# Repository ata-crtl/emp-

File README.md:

**COMPLETE EMP BUILD**

  This is a low energy through hole electro magnetic pulse generator built for educational purposes.
  It uses inductive Kicback from a simple air core coil to generate broad band pulse that can glitch or reset unshielded digital circuits. Flip the top saftey , then you hold down the trigger for 2 seconds to fire max.

Onshape link = https://cad.onshape.com/documents/e3ea2a8dce756d3e28ba0ed2/w/b44164742f645132d3413e84/e/23451d8a78cdce11df78b1ae?renderMode=0&uiState=6a40249c9a392f71b3cf0f7e
  ---

 ## Table of Contents

- [What is this?](#what-is-this)
- [Why I built it](#why-i-built-it)
- [How it works (in 30 secs)](#how-it-works-in-30-secs)
- [Images and diagrams](#images-and-diagrams)
- [Assembly instructions](#assembly-instructions)
  - [1. Solder the PCB](#1-solder-the-pcb)
  - [2. Wind the coil](#2-wind-the-coil)
  - [3. Prepare the enclosure](#3-prepare-the-enclosure)
  - [4. Final assembly](#4-final-assembly)
- [Safety precautions](#safety-precautions)

---

## What is this?
 A compact, battery powered device that creates a rapid magnetic field collapse,radiating an electro magnetic pulse strong enough to inter fere with nearby digital electronics.It is not a weapon.EDUCTIONAL  USE ONLY

**KEY SPECS**
|parameter|Value|
|-------|--------|
|Pulse voltage at coil|>200V|
|Effective range |20-30cm(glitch)|
|power supply|3s lipo(11.1v)|
|Max fire time|2 seconds(thermal limit) more = you have 3 seconds to get out  :)|

---

## Why I built it
I always saw lots of tutorials on youtube and always thought how cool they looked.So i thought why not build it, but most of the tutorials on youtube were either weak emps or were very vauge on how to build it.

---
## How it works (in 30 secs)
- 1. A boost converter charges a bank of capacitors to 18V
  2. A 555 timer generates a short pulse,when you press the button
  3. That pulse drives a tc4420 gate driver which turns on the mosfet
  4. Current builds up at the air core coil for like a millisecond
  5. when the mosfet turns of the magnetic field collapses
  6. This makes a voltage spike  which goes over 200v and radiates abroad band emp

---

## Images and diagrams

---
## Assembly instructions
Get your pcb made, the gerber files are in the github.All components are marked on the pcb.
 ## 1. Solder the PCB
1. solder in order of hight, solder in resistors(r1-r7),small ceramics(c1,c5,c7)
 - then u1,u2,u3
 - then d1,l1,j1,j2,j3,j4
 - capacitors,c2,c3,c4,c6 . mind the polarity
 - q1 mossfet last
   
  2.clean the board with isopropyl alcohol
   
## 2. Wind the coil

- 1.Cut 40 cm of the 14awg magnet wire

  2.find a 2cm diameter cylinder(pen.pipe ect)

  3.wind 12 tight turns,make sure they touch

  4.slide it of, wrap with electrical tape

  5. leave  5cm at the end and strip the enamel and tin

  6. twist the 2 leads together

  7. measure resistance. should be 1-3 ohms . if lower add a 1 ohm resistor in series.

 ## 3. Prepare the enclosure
  
  -get the 3d printed case and line all the interior walls with copper foil other than the round emmesion  window at the front, cover the grills as well, but they are for heat dissapation.
  
  -overlap the foil and solder for continuity if needed

  ` solder 1 piece of wire to the foil and the other end to j4 for gnd
  
  ## 4. Final assembly
  1.mount the coil inside the case using hot glue,keep the twisted leads pointing towards the pcb area.

  2. place the battery in the top compartment , insert the heat set inserts , and screw the lid down, make sure the wires exit throught the bottom, slide on to the top of the case

  3.connect the  off board components.
 
  |Component A |Component B|
  |------------|-----------|
  |battery+|fuse|
  |fuse|master switch|
  |master switch|j2 pin 1 batt+(on pcb)|
  |battery-|j2 pin 2 batt-(on pcb)|
  |j3 pin 1 |one side of button|
  |other side of button|j3 pin2|
  |coil lead one side|j1|
  |coil lead other side|j2|

  4.place the pcb into the case and secure using the mounting holes ,use the m2 screws. 
  5. place the heat set inserts and screw the case shut.
  
----- 
## Safety precautions

. keep body and head 20-30 cm from emission window

.always discharge the coil after use, do not touch the coil while on

.do not use near pace makers , medical implants or sensitive lab equipment.

.keep a class c fire extinguisher nearby.

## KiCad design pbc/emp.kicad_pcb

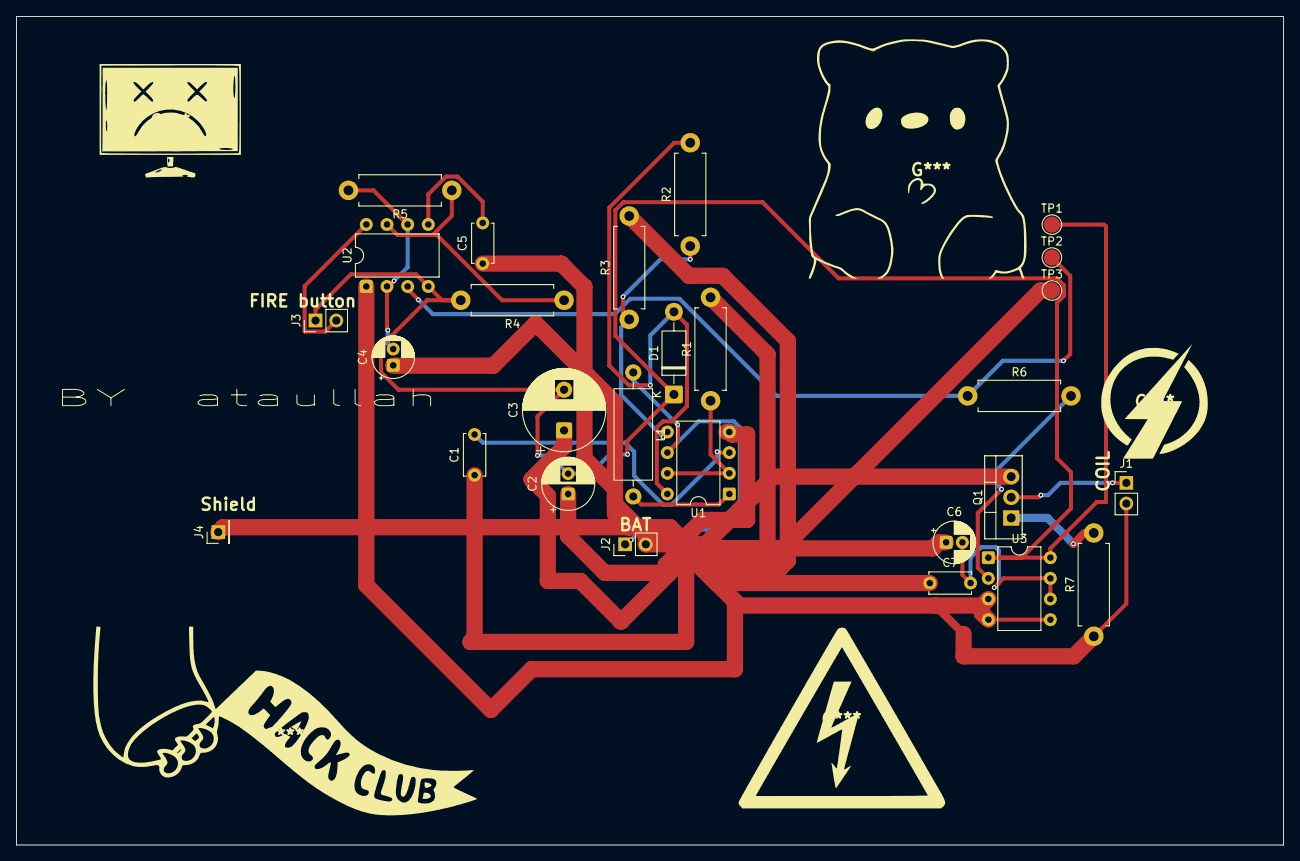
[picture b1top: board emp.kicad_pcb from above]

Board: 2 copper layers, 155.7 x 101.8 mm, 27 parts (0 on the bottom side), 17 nets.

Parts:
C1: 1n; C_Disc_D5.0mm_W2.5mm_P5.00mm
C2: 100u; CP_Radial_D6.3mm_P2.50mm
C3: 1000u; CP_Radial_D10.0mm_P5.00mm
C4, C6: 10u; CP_Radial_D5.0mm_P2.00mm
C5: 10n; C_Disc_D4.7mm_W2.5mm_P5.00mm
C7: 0.1u; C_Disc_D5.0mm_W2.5mm_P5.00mm
D1: 1N5819; D_DO-41_SOD81_P10.16mm_Horizontal
J1: COIL; PinHeader_1x02_P2.54mm_Vertical
J2: BAT; PinHeader_1x02_P2.54mm_Vertical
J3: BTN; PinHeader_1x02_P2.54mm_Vertical
J4: FOIL_GND; PinHeader_1x01_P2.54mm_Vertical
L1: 100u; L_Axial_L11.0mm_D4.5mm_P15.24mm_Horizontal_Fastron_MECC
Q1: IRF540N; TO-220-3_Vertical
R1: 0.22; R_Axial_DIN0411_L9.9mm_D3.6mm_P12.70mm_Horizontal
R2: 10k; R_Axial_DIN0411_L9.9mm_D3.6mm_P12.70mm_Horizontal
R3: 2.2k; R_Axial_DIN0411_L9.9mm_D3.6mm_P12.70mm_Horizontal
R4, R5: 100k; R_Axial_DIN0411_L9.9mm_D3.6mm_P12.70mm_Horizontal
R6: 1k; R_Axial_DIN0411_L9.9mm_D3.6mm_P12.70mm_Horizontal
R7: 10; R_Axial_DIN0411_L9.9mm_D3.6mm_P12.70mm_Horizontal
TP1, TP2, TP3: TestPoint; TestPoint_Pad_D2.0mm
U1: MC34063AP; DIP-8_W7.62mm
U2: NE555P; DIP-8_W7.62mm
U3: TC4420CPA; DIP-8_W7.62mm

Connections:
+18v: C2.2, C3.2, D1.1 (K), J3.1, R4.2, TP1.1 (1_1), U2.4 (~RST), U3.1 (VDD), U3.8 (VDD)
/L1 to Bat j2 1: J2.1, L1.1, U1.6 (Vin)
/q1,j1: J1.1, Q1.2 (D)
/r6 , u3 2: R6.2, U3.2 (INPUT)
/r7,q1: Q1.1 (G), R7.2
/u1 2 , r1: R1.1, U1.2 (SwE), U1.7 (Ipk)
/u1 3 C1: C1.2, U1.3 (TC)
/u1 5, r2 ,r3: R2.1, R3.1, U1.5 (Vfb)
/u1 8 , r2: D1.2 (A), R2.2, U1.8 (DC)
/u1,1 to l1: L1.2, U1.1 (SwC)
/u2 2 ,c4: C4.2, R5.2, U2.2 (TRIG), U2.6 (THRES)
/u2 3 ,tp2: R6.1, TP2.1 (1_1), U2.3 (OUT)
/u2 5 ,c5: C5.2, U2.5 (CONT)
/u2 7,r4 , r5: R4.1, R5.1, U2.7 (DISCH)
/u2 8,j3 2: J3.2, U2.8 (VCC)
/u3 6,c6,c7: C6.2, C7.2, U3.6 (OUTPUT), U3.7 (OUTPUT)
GND: C1.1, C2.1, C3.1, C4.1, C5.1, C6.1, C7.1, J1.2, J2.2, J4.1 (Pin_1_1), Q1.3 (S), R1.2, R3.2, R7.1, TP3.1 (1_1), U1.4 (GND), U2.1 (GND), U3.3 (NC), U3.4 (GND), U3.5 (GND)

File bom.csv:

Refrence,part,amount,Price(£),link
pcb hardware,,,,
J1,"2 pin screw terminal,5.08 pitch,throught hole",1,0.99,https://www.aliexpress.com/i/1005001666625465.html
J2,"2 pin screw terminal,5.08 pitch,throught hole",1,0.99,https://www.aliexpress.com/i/1005001666625465.html
J3,"2 pin screw terminal,2.54 pitch,throught hole",1,1.9,https://www.aliexpress.com/item/1005003629262239.html
J4,1 pin header,1,0.97,https://www.aliexpress.com/item/1005005574179742.html?spm=a2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
F1,"2A,slow blow fuse + inline fuse holder",1,0.99,https://www.aliexpress.com/item/1005010608703257.html?spm=a2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
s1,spst toggle switch,1,2.32,"https://www.aliexpress.com/item/1005005937082827.html?spm=a2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
"
s2,spst momentory push button,1,0.64,https://www.aliexpress.com/item/1005003807410534.html?spm=a2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
,"copper foil tape,50mm width",1,4.14,https://www.aliexpress.com/item/1005010583224519.html?spm=a2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
semi conductor,,,,
u1,MC34063AP(boost converter),1,1.26,https://www.aliexpress.com/item/1005006918896712.html?spm=a2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
u2,NE555p(timer),1,0.99,https://www.aliexpress.com/item/1005009339787324.html?spm=a2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
u3,TC4420CPA(mossfet driver),1,4,https://www.aliexpress.com/item/1005012098576784.html?spm=a2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
q1,IRFZ44N,1,1.91,https://www.aliexpress.com/item/1005008166831325.html?spm=a2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
d1,1N5819,1,1.88,https://www.aliexpress.com/item/1005007807556976.html?spm=a2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
INDCTORS,,,,
l1,"100uH ,1a rated radial",1,0.51,https://www.aliexpress.com/item/1005006119088521.html?spm=a2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
RESISTORS,,,,
r1,"022 ohms , 2w,axial",1,0.66,https://www.aliexpress.com/item/1005007170526978.html?spm=a2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
r2,"10k ohms , 1/4 w",1,0.53,https://www.aliexpress.com/item/1005002489867848.html?spm=a2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
r3,2.2k ohms1/4 w,1,0.5,https://www.aliexpress.com/item/1005007330288041.html?spm=a2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
r4,"100k ohms , 1/4 ohms",1,1.51,https://www.aliexpress.com/item/1005004002774546.html?spm=a2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
r5,"100k ohms , 1/4 ohms",1,1.51,https://www.aliexpress.com/item/1005004002774546.html?spm=a2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
r6,"1k ohms, 1/4 W",1,0.53,https://www.aliexpress.com/item/1005002489867848.html?spm=a2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
r7,"10 ohms , 1/4 W",1,1.75,https://www.aliexpress.com/item/1005004961926843.html?spm=a2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
capacitors,,,,
c1,"1nF , 50V , cermaic",1,0.24,https://www.aliexpress.com/item/1005003584800244.html?spm=a2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
c2,"100uF,25v,electrolytic",1,1.1,https://www.aliexpress.com/item/1005011631970768.html?spm=a2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
c3,"1000uF,25v,electrolytic",1,2.1,https://www.aliexpress.com/item/1005011631970768.html?spm=a2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
c4,"10uF,25v,electrolytic",1,2.1,https://www.aliexpress.com/item/1005011631970768.html?spm=a2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
c5,"10nfF,50v,cermaic",1,0.99,https://www.aliexpress.com/item/1005012084843800.html?spm=a2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
c6,"10uF,25v,electrolytic",1,2.1,https://www.aliexpress.com/item/1005011631970768.html?spm=a2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
c7,"0.1uf, 50V,cermaic",1,0.24,https://www.aliexpress.com/item/1005003584800244.html?spm=a2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
,heat set inserts ,4,0.99,https://www.aliexpress.com/item/1005008666672949.html?spm=a2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
,14 awg enammell coated copper wire,1,2.37,https://www.aliexpress.com/item/1005005549459084.html?spm=a2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

Total,,,42,

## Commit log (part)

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2026-05-26 Rename emp bom.csv - Sheet1.csv to bom.csv
2026-05-26 Create 3d models
2026-05-26 Create random
2026-05-26 Create randomm
2026-05-26 Rename randomm to fd
2026-05-26 Rename .step to .step
2026-05-28 Create edrftgyu
